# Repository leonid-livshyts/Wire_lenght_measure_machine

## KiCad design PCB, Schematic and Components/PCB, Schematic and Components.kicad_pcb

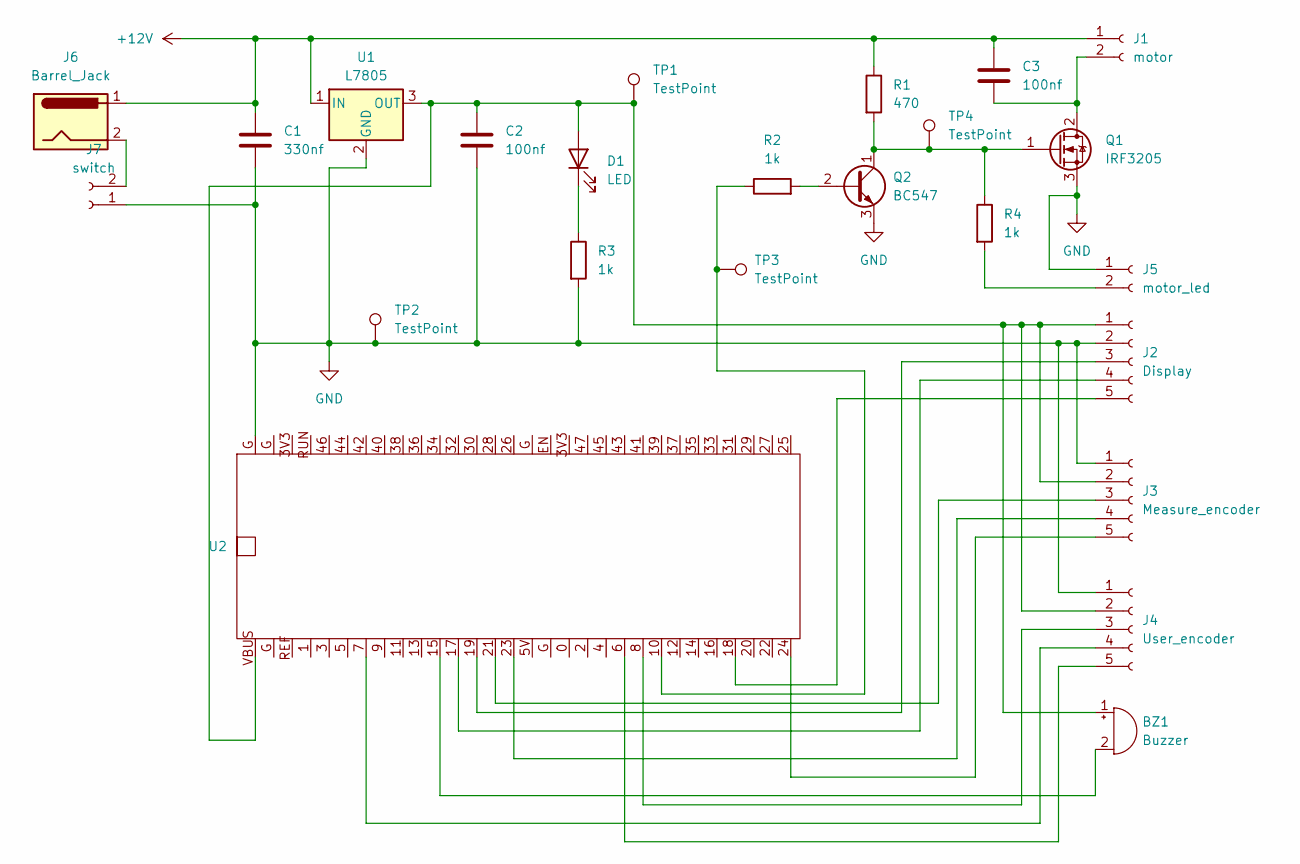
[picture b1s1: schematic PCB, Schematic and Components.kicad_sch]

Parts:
BZ1: Buzzer; Buzzer_12x9.5RM7.6
C1: 330nf; C_Disc_D3.8mm_W2.6mm_P2.50mm
C2, C3: 100nf; C_Disc_D3.8mm_W2.6mm_P2.50mm
D1: LED; LED_D5.0mm
J1: motor; AMASS_XT30U-F_1x02_P5.0mm_Vertical
J2: Display; Hirose_DF13-05P-1.25DSA_1x05_P1.25mm_Vertical
J3: Measure_encoder; Hirose_DF13-05P-1.25DSA_1x05_P1.25mm_Vertical
J4: User_encoder; Hirose_DF13-05P-1.25DSA_1x05_P1.25mm_Vertical
J5: motor_led; Hirose_DF13-02P-1.25DSA_1x02_P1.25mm_Vertical
J6: Barrel_Jack; BarrelJack_SwitchcraftConxall_RAPC10U_Horizontal
J7: switch; AMASS_XT30U-F_1x02_P5.0mm_Vertical
Q1: IRF3205; TO-220-3_Vertical
Q2: BC547; TO-92_Inline
R1: 470; R_Axial_DIN0207_L6.3mm_D2.5mm_P10.16mm_Horizontal
R2, R3, R4: 1k; R_Axial_DIN0207_L6.3mm_D2.5mm_P10.16mm_Horizontal
TP1, TP2, TP3, TP4: TestPoint; Pin_D0.7mm_L6.5mm_W1.8mm_FlatFork
U1: L7805; TO-220F-3_Vertical
U2: WeAct2350B

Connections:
+12V: C1.1, C3.1, J1.1, J6.1, R1.1, U1.1 (IN)
GND: C1.2, C2.2, J2.2, J3.1, J4.1, J5.1, J7.1, Q1.3 (S), Q2.3 (E), R3.2, TP2.1 (1_1), U1.2 (GND), U2.G
unnamed: BZ1.1 (+), C2.1, D1.2 (A), J2.1, J3.2, J4.2, TP1.1 (1_1), U1.3 (OUT), U2.VBUS
unnamed: BZ1.2 (-), U2.15
unnamed: D1.1 (K), R3.1
unnamed: C3.2, J1.2, Q1.2 (D)
unnamed: J2.3, U2.19
unnamed: J2.4, U2.17
unnamed: J2.5, U2.18
unnamed: J3.3, U2.21
unnamed: J3.4, U2.23
unnamed: J3.5, U2.24
unnamed: J4.3, U2.8
unnamed: J4.4, U2.7
unnamed: J4.5, U2.6
unnamed: J5.2, R4.2
unnamed: J6.2, J7.2
unnamed: Q1.1 (G), Q2.1 (C), R1.2, R4.1, TP4.1 (1_1)
unnamed: Q2.2 (B), R2.2
unnamed: R2.1, TP3.1 (1_1), U2.10

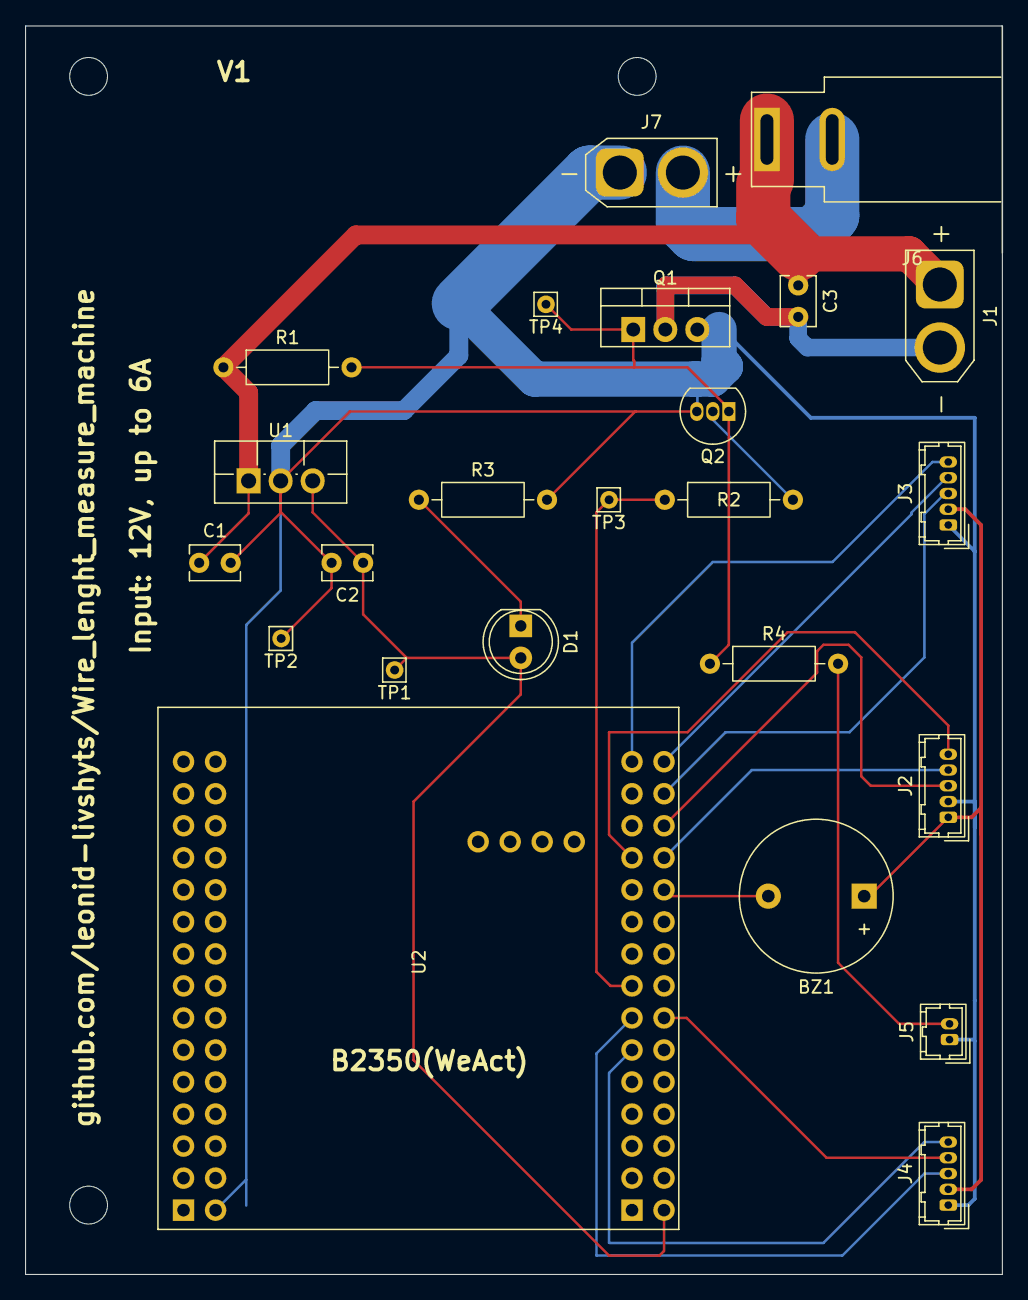
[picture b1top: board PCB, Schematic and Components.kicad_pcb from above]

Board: 2 copper layers, 77.5 x 99.0 mm, 24 parts (0 on the bottom side), 20 nets.
